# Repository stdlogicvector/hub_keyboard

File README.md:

# HUB Keyboard

A custom built 80% keyboard with an OLED and an integrated USB hub.

(The  can be found here.)

## Circuit Board

The circuit board is designed in Eagle.
For easy manufacturing, the gerber-files and SMT production files are included.

The BOM and SMT placement file (CPL) are formatted for use with JLCPCB.

Apart from the keys, display, and the USB-connector all parts can be populated by JLCPCB.
The schematic contains the LCSC partnumbers in the attributes of each part.

### JLCPCB Configuration

If you want to order PCBs from JLC-PCB with the provided gerber-files,
use the following settings after uploading the zipped gerber folder:

* Layers: 2
* Dimension: 362mm x 128.5mm
* PCB Color: Choose what you want
* PCB Thickness: 1.6
* Impedance: no
* Surface Finish: HASL(with lead) (ENIG is also OK)
* Copper Weight: 1
* Gold Fingers: No
* Material Details: FR4-Standard Tg 130-140C
* Panel By JLCPCB: No
* Flying Probe Test: Fully Test
* Castellated Holes: no
* Different Design: 1
* Remove Order Number: Choose what you want

5 PCBs without assembly cost about 17.35€ or $19.60.

If you want to have the SMT parts populated, choose "SMT Assembly" and select "Bottom Layer".

When asked for the BOM and CPL file, upload the provided files.

Assembly and parts for 5 PCBs costs about 45.50€ or $55.90.

### Keys

All keys compatible with Cherry MX 2 or 3 pin should fit the board.
There a mounting holes for the US-layout (with 2.25U Left Shift) and the EU-layout (with <> next to 1.25U Left Shift).
The Spacebar can also be replaced by up 5 individual keys.

### Display

The display is an 0.91" 128x32 SPI OLED module like [this](https://www.ebay.com/itm/312892164528). They are all over ebay and aliexpress.

### Misc Parts

The USB Connectors can be found on Digikey, but you can substitute others with the same pad layout.#

* USB-C : [Digikey](https://www.digikey.com/short/zm17vb)
* USB-A : [Digikey](https://www.digikey.com/short/zm1tcc)

## QMK Configuration

The folder qmk_config contains the configuration and code to build QMK for the HUB-Keyboard.
Just put this folder in qmk/keyboards and run

```
make hub_keyboard/v1:default
```	
	
## Plate & Case

Plate and Case are available as DXF and STL files. The Case also comes in two halves for easier printing. The DXF contains lines for both layout options at the left shift key. Delete what you don't need before cutting.

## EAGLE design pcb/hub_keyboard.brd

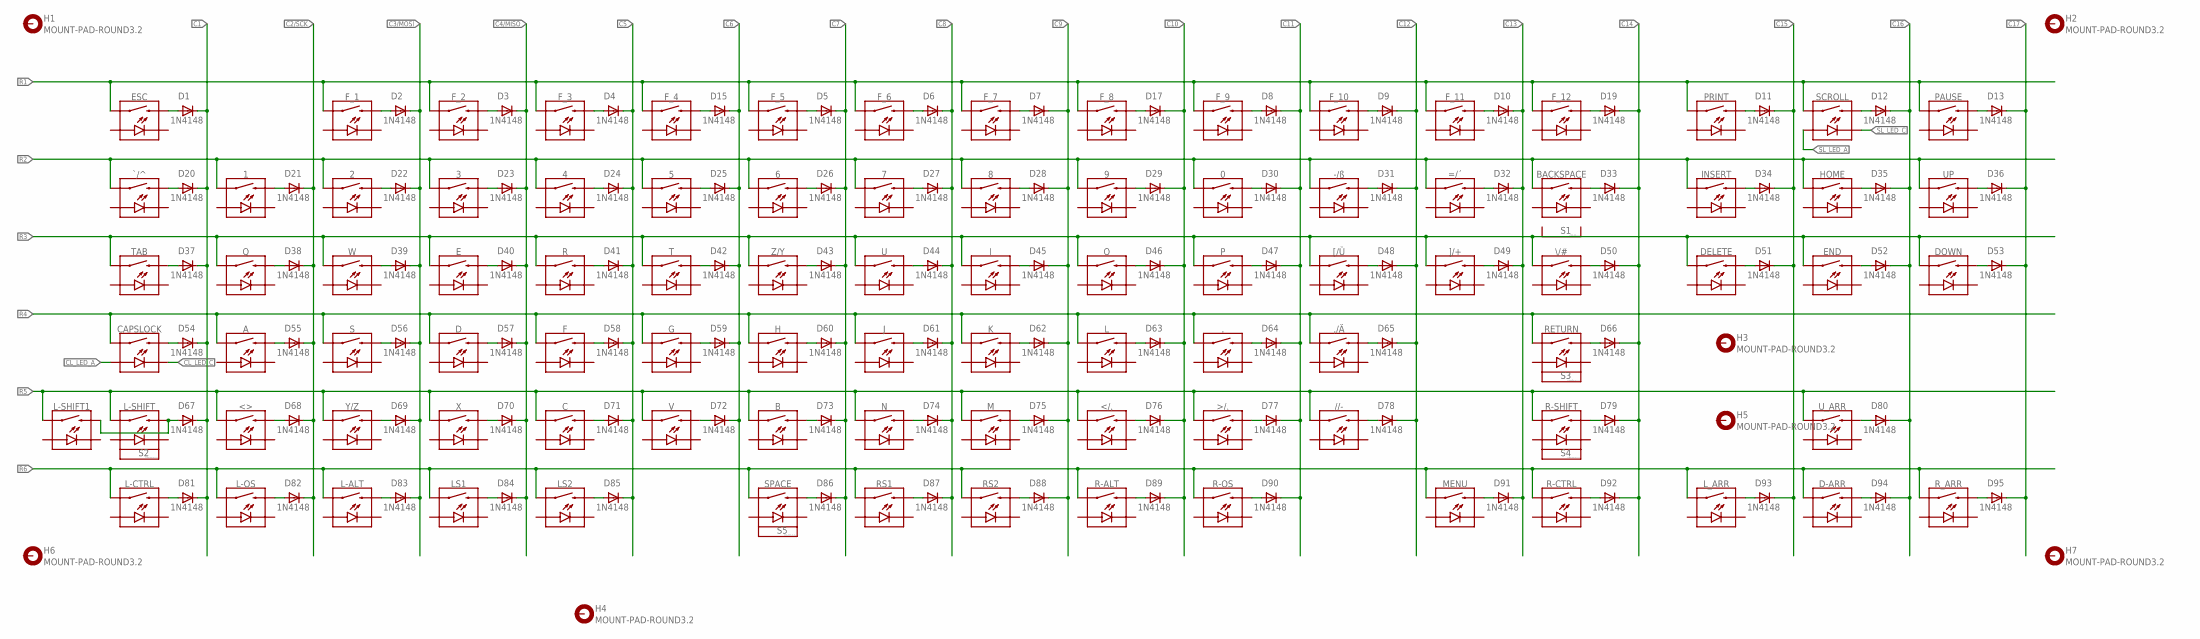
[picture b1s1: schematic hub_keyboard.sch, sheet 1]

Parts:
0, 1, 2, 3, 4, 5, 6, 7, 8, 9, .: MECHANICAL-KEYBOARD1U; CHERRY-MX-LED-1U
,/Ä: MECHANICAL-KEYBOARD1U; CHERRY-MX-LED-1U
-/ß: MECHANICAL-KEYBOARD1U; CHERRY-MX-LED-1U
//-: MECHANICAL-KEYBOARD1U; CHERRY-MX-LED-1U
</,: MECHANICAL-KEYBOARD1U; CHERRY-MX-LED-1U
<>: MECHANICAL-KEYBOARD1U; CHERRY-MX-LED-1U
=/´: MECHANICAL-KEYBOARD1U; CHERRY-MX-LED-1U
>/.: MECHANICAL-KEYBOARD1U; CHERRY-MX-LED-1U
A: MECHANICAL-KEYBOARD1U; CHERRY-MX-LED-1U
B: MECHANICAL-KEYBOARD1U; CHERRY-MX-LED-1U
BACKSPACE: MECHANICAL-KEYBOARD2U; CHERRY-MX-LED-1X2U
C: MECHANICAL-KEYBOARD1U; CHERRY-MX-LED-1U
CAPSLOCK: MECHANICAL-KEYBOARD1.75U; CHERRY-MX-LED-1.75U
D: MECHANICAL-KEYBOARD1U; CHERRY-MX-LED-1U
D1, D2, D3, D4, D5, D6, D7, D8, D9, D10, D11, D12, D13, D15, D17, D19, D20, D21, D22, D23, D24, D25, D26, D27, D28, D29, D30, D31, D32, D33, D34, D35, D36, D37, D38, D39, D40, D41, D42, D43, D44, D45, D46, D47, D48, D49, D50, D51, D52, D53, D54, D55, D56, D57, D58, D59, D60, D61, D62, D63, D64, D65, D66, D67, D68, D69, D70, D71, D72, D73, D74, D75, D76, D77, D78, D79, D80, D81, D82, D83, D84, D85, D86, D87, D88, D89, D90, D91, D92, D93, D94, D95: 1N4148; SOD123; LCSC C81598
D-ARR: MECHANICAL-KEYBOARD1U; CHERRY-MX-LED-1U
DELETE: MECHANICAL-KEYBOARD1U; CHERRY-MX-LED-1U
DOWN: MECHANICAL-KEYBOARD1U; CHERRY-MX-LED-1U
E: MECHANICAL-KEYBOARD1U; CHERRY-MX-LED-1U
END: MECHANICAL-KEYBOARD1U; CHERRY-MX-LED-1U
ESC: MECHANICAL-KEYBOARD1U; CHERRY-MX-LED-1U
F: MECHANICAL-KEYBOARD1U; CHERRY-MX-LED-1U
F_1, F_2, F_3, F_4, F_5, F_6, F_7, F_8, F_9, F_10, F_11, F_12: MECHANICAL-KEYBOARD1U; CHERRY-MX-LED-1U
G: MECHANICAL-KEYBOARD1U; CHERRY-MX-LED-1U
H: MECHANICAL-KEYBOARD1U; CHERRY-MX-LED-1U
H1, H2, H3, H4, H5, H6, H7: MOUNT-PAD-ROUND3.2; 3,2-PAD
HOME: MECHANICAL-KEYBOARD1U; CHERRY-MX-LED-1U
I: MECHANICAL-KEYBOARD1U; CHERRY-MX-LED-1U
INSERT: MECHANICAL-KEYBOARD1U; CHERRY-MX-LED-1U
J: MECHANICAL-KEYBOARD1U; CHERRY-MX-LED-1U
K: MECHANICAL-KEYBOARD1U; CHERRY-MX-LED-1U
L: MECHANICAL-KEYBOARD1U; CHERRY-MX-LED-1U
L-ALT: MECHANICAL-KEYBOARD1.25U; CHERRY-MX-LED-1.25U
L-CTRL: MECHANICAL-KEYBOARD1.25U; CHERRY-MX-LED-1.25U
L-OS: MECHANICAL-KEYBOARD1.25U; CHERRY-MX-LED-1.25U
L-SHIFT: MECHANICAL-KEYBOARD2.25U; CHERRY-MX-LED-1X2.25
L-SHIFT1: MECHANICAL-KEYBOARD1.25U; CHERRY-MX-LED-1.25U
LS1, LS2: MECHANICAL-KEYBOARD1.25U; CHERRY-MX-LED-1.25U
L_ARR: MECHANICAL-KEYBOARD1U; CHERRY-MX-LED-1U
M: MECHANICAL-KEYBOARD1U; CHERRY-MX-LED-1U
MENU: MECHANICAL-KEYBOARD1.25U; CHERRY-MX-LED-1.25U
N: MECHANICAL-KEYBOARD1U; CHERRY-MX-LED-1U
O: MECHANICAL-KEYBOARD1U; CHERRY-MX-LED-1U
P: MECHANICAL-KEYBOARD1U; CHERRY-MX-LED-1U
PAUSE: MECHANICAL-KEYBOARD1U; CHERRY-MX-LED-1U
PRINT: MECHANICAL-KEYBOARD1U; CHERRY-MX-LED-1U
Q: MECHANICAL-KEYBOARD1U; CHERRY-MX-LED-1U
R: MECHANICAL-KEYBOARD1U; CHERRY-MX-LED-1U
R-ALT: MECHANICAL-KEYBOARD1.25U; CHERRY-MX-LED-1.25U
R-CTRL: MECHANICAL-KEYBOARD1.25U; CHERRY-MX-LED-1.25U
R-OS: MECHANICAL-KEYBOARD1.25U; CHERRY-MX-LED-1.25U
R-SHIFT: MECHANICAL-KEYBOARD2.75U; CHERRY-MX-LED-1X2.75
RETURN: MECHANICAL-KEYBOARD2.25U; CHERRY-MX-LED-1X2.25
RS1, RS2: MECHANICAL-KEYBOARD1.25U; CHERRY-MX-LED-1.25U
R_ARR: MECHANICAL-KEYBOARD1U; CHERRY-MX-LED-1U
S: MECHANICAL-KEYBOARD1U; CHERRY-MX-LED-1U
S1: STABILIZER-1X2U; STABILIZER_1X2U
S2, S3: STABILIZER-1X2.25U; STABILIZER_1X2.25U
S4: STABILIZER-1X2.75U; STABILIZER_1X2.75U
S5: STABILIZER-1X6.25U; STABILIZER_1X6.25U
SCROLL: MECHANICAL-KEYBOARD1U; CHERRY-MX-LED-1U
SPACE: MECHANICAL-KEYBOARD6.25U; CHERRY-MX-LED-1X6.25
T: MECHANICAL-KEYBOARD1U; CHERRY-MX-LED-1U
TAB: MECHANICAL-KEYBOARD1.5U; CHERRY-MX-LED-1.5U
U: MECHANICAL-KEYBOARD1U; CHERRY-MX-LED-1U
UP: MECHANICAL-KEYBOARD1U; CHERRY-MX-LED-1U
U_ARR: MECHANICAL-KEYBOARD1U; CHERRY-MX-LED-1U
V: MECHANICAL-KEYBOARD1U; CHERRY-MX-LED-1U
W: MECHANICAL-KEYBOARD1U; CHERRY-MX-LED-1U
X: MECHANICAL-KEYBOARD1U; CHERRY-MX-LED-1U
Y/Z: MECHANICAL-KEYBOARD1U; CHERRY-MX-LED-1U
Z/Y: MECHANICAL-KEYBOARD1U; CHERRY-MX-LED-1U
[/Ü: MECHANICAL-KEYBOARD1U; CHERRY-MX-LED-1U
\\/#: MECHANICAL-KEYBOARD1.5U; CHERRY-MX-LED-1.5U
]/+: MECHANICAL-KEYBOARD1U; CHERRY-MX-LED-1U
`/^: MECHANICAL-KEYBOARD1U; CHERRY-MX-LED-1U

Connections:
C1: D1.C, D20.C, D37.C, D54.C, D67.C, D81.C; also elsewhere on the board
C2/SCK: D21.C, D38.C, D55.C, D68.C, D82.C; also elsewhere on the board
C3/MOSI: D2.C, D22.C, D39.C, D56.C, D69.C, D83.C; also elsewhere on the board
C4/MISO: D3.C, D23.C, D40.C, D57.C, D70.C, D84.C; also elsewhere on the board
C5: D4.C, D24.C, D41.C, D58.C, D71.C, D85.C; also elsewhere on the board
C6: D15.C, D25.C, D42.C, D59.C, D72.C; also elsewhere on the board
C7: D5.C, D26.C, D43.C, D60.C, D73.C, D86.C; also elsewhere on the board
C8: D6.C, D27.C, D44.C, D61.C, D74.C, D87.C; also elsewhere on the board
C9: D7.C, D28.C, D45.C, D62.C, D75.C, D88.C; also elsewhere on the board
C10: D17.C, D29.C, D46.C, D63.C, D76.C, D89.C; also elsewhere on the board
C11: D8.C, D30.C, D47.C, D64.C, D77.C, D90.C; also elsewhere on the board
C12: D9.C, D31.C, D48.C, D65.C, D78.C; also elsewhere on the board
C13: D10.C, D32.C, D49.C, D91.C; also elsewhere on the board
C14: D19.C, D33.C, D50.C, D66.C, D79.C, D92.C; also elsewhere on the board
C15: D11.C, D34.C, D51.C, D93.C; also elsewhere on the board
C16: D12.C, D35.C, D52.C, D80.C, D94.C; also elsewhere on the board
C17: D13.C, D36.C, D53.C, D95.C; also elsewhere on the board
CL_LED_A: CAPSLOCK.A; also elsewhere on the board
CL_LED_C: CAPSLOCK.K (C); also elsewhere on the board
unnamed: D11.A, PRINT.S2 (2)
unnamed: D34.A, INSERT.S2 (2)
unnamed: D51.A, DELETE.S2 (2)
unnamed: D12.A, SCROLL.S2 (2)
unnamed: D35.A, HOME.S2 (2)
unnamed: D93.A, L_ARR.S2 (2)
unnamed: D52.A, END.S2 (2)
unnamed: D80.A, U_ARR.S2 (2)
unnamed: D94.A, D-ARR.S2 (2)
unnamed: D13.A, PAUSE.S2 (2)
unnamed: D36.A, UP.S2 (2)
unnamed: D53.A, DOWN.S2 (2)
unnamed: <>.S2 (2), D68.A
unnamed: D95.A, R_ARR.S2 (2)
unnamed: D1.A, ESC.S2 (2)
unnamed: D20.A, `/^.S2 (2)
unnamed: D37.A, TAB.S2 (2)
unnamed: CAPSLOCK.S2 (2), D54.A
unnamed: D67.A, L-SHIFT.S2 (2), L-SHIFT1.S2 (2)
unnamed: D81.A, L-CTRL.S2 (2)
unnamed: 1.S2 (2), D21.A
unnamed: D38.A, Q.S2 (2)
unnamed: A.S2 (2), D55.A
unnamed: D69.A, Y/Z.S2 (2)
unnamed: D82.A, L-OS.S2 (2)
unnamed: D2.A, F_1.S2 (2)
unnamed: 2.S2 (2), D22.A
unnamed: D39.A, W.S2 (2)
unnamed: D56.A, S.S2 (2)
unnamed: D70.A, X.S2 (2)
unnamed: D83.A, L-ALT.S2 (2)
unnamed: D3.A, F_2.S2 (2)
unnamed: 3.S2 (2), D23.A
unnamed: D40.A, E.S2 (2)
unnamed: D.S2 (2), D57.A
unnamed: C.S2 (2), D71.A
unnamed: D4.A, F_3.S2 (2)
unnamed: 4.S2 (2), D24.A
unnamed: D41.A, R.S2 (2)
unnamed: D58.A, F.S2 (2)
unnamed: D72.A, V.S2 (2)
unnamed: D15.A, F_4.S2 (2)
unnamed: 5.S2 (2), D25.A
unnamed: D42.A, T.S2 (2)
unnamed: D59.A, G.S2 (2)
unnamed: B.S2 (2), D73.A
unnamed: D86.A, SPACE.S2 (2)
unnamed: D5.A, F_5.S2 (2)
unnamed: 6.S2 (2), D26.A
unnamed: D43.A, Z/Y.S2 (2)
unnamed: D60.A, H.S2 (2)
unnamed: D74.A, N.S2 (2)
unnamed: D6.A, F_6.S2 (2)
unnamed: 7.S2 (2), D27.A
unnamed: D44.A, U.S2 (2)
unnamed: D61.A, J.S2 (2)
unnamed: D75.A, M.S2 (2)
unnamed: D7.A, F_7.S2 (2)
unnamed: 8.S2 (2), D28.A
unnamed: D45.A, I.S2 (2)
unnamed: D62.A, K.S2 (2)
unnamed: </,.S2 (2), D76.A
unnamed: D17.A, F_8.S2 (2)
unnamed: 9.S2 (2), D29.A
unnamed: D46.A, O.S2 (2)
unnamed: D63.A, L.S2 (2)
unnamed: >/..S2 (2), D77.A
unnamed: D89.A, R-ALT.S2 (2)
unnamed: D8.A, F_9.S2 (2)
unnamed: 0.S2 (2), D30.A
unnamed: D47.A, P.S2 (2)
unnamed: ..S2 (2), D64.A
unnamed: //-.S2 (2), D78.A
unnamed: D90.A, R-OS.S2 (2)
unnamed: D9.A, F_10.S2 (2)
unnamed: -/ß.S2 (2), D31.A
unnamed: D48.A, [/Ü.S2 (2)
unnamed: ,/Ä.S2 (2), D65.A
unnamed: D10.A, F_11.S2 (2)
unnamed: =/´.S2 (2), D32.A
unnamed: D49.A, ]/+.S2 (2)
unnamed: D91.A, MENU.S2 (2)
unnamed: D19.A, F_12.S2 (2)
unnamed: BACKSPACE.S2 (2), D33.A
unnamed: D50.A, \\/#.S2 (2)
unnamed: D66.A, RETURN.S2 (2)
unnamed: D79.A, R-SHIFT.S2 (2)
unnamed: D92.A, R-CTRL.S2 (2)
unnamed: D85.A, LS2.S2 (2)
unnamed: D84.A, LS1.S2 (2)
unnamed: D88.A, RS2.S2 (2)
unnamed: D87.A, RS1.S2 (2)
R1: ESC.S1 (1), F_1.S1 (1), F_2.S1 (1), F_3.S1 (1), F_4.S1 (1), F_5.S1 (1), F_6.S1 (1), F_7.S1 (1), F_8.S1 (1), F_9.S1 (1), F_10.S1 (1), F_11.S1 (1), F_12.S1 (1), PAUSE.S1 (1), PRINT.S1 (1), SCROLL.S1 (1); also elsewhere on the board
R2: 0.S1 (1), 1.S1 (1), 2.S1 (1), 3.S1 (1), 4.S1 (1), 5.S1 (1), 6.S1 (1), 7.S1 (1), 8.S1 (1), 9.S1 (1), -/ß.S1 (1), =/´.S1 (1), BACKSPACE.S1 (1), HOME.S1 (1), INSERT.S1 (1), UP.S1 (1), `/^.S1 (1); also elsewhere on the board
R3: DELETE.S1 (1), DOWN.S1 (1), E.S1 (1), END.S1 (1), I.S1 (1), O.S1 (1), P.S1 (1), Q.S1 (1), R.S1 (1), T.S1 (1), TAB.S1 (1), U.S1 (1), W.S1 (1), Z/Y.S1 (1), [/Ü.S1 (1), \\/#.S1 (1), ]/+.S1 (1); also elsewhere on the board
R4: ,/Ä.S1 (1), ..S1 (1), A.S1 (1), CAPSLOCK.S1 (1), D.S1 (1), F.S1 (1), G.S1 (1), H.S1 (1), J.S1 (1), K.S1 (1), L.S1 (1), RETURN.S1 (1), S.S1 (1); also elsewhere on the board
R5: //-.S1 (1), </,.S1 (1), <>.S1 (1), >/..S1 (1), B.S1 (1), C.S1 (1), L-SHIFT.S1 (1), L-SHIFT1.S1 (1), M.S1 (1), N.S1 (1), R-SHIFT.S1 (1), U_ARR.S1 (1), V.S1 (1), X.S1 (1), Y/Z.S1 (1); also elsewhere on the board
R6: D-ARR.S1 (1), L-ALT.S1 (1), L-CTRL.S1 (1), L-OS.S1 (1), LS1.S1 (1), LS2.S1 (1), L_ARR.S1 (1), MENU.S1 (1), R-ALT.S1 (1), R-CTRL.S1 (1), R-OS.S1 (1), RS1.S1 (1), RS2.S1 (1), R_ARR.S1 (1), SPACE.S1 (1); also elsewhere on the board
SL_LED_A: SCROLL.A; also elsewhere on the board
SL_LED_C: SCROLL.K (C); also elsewhere on the board

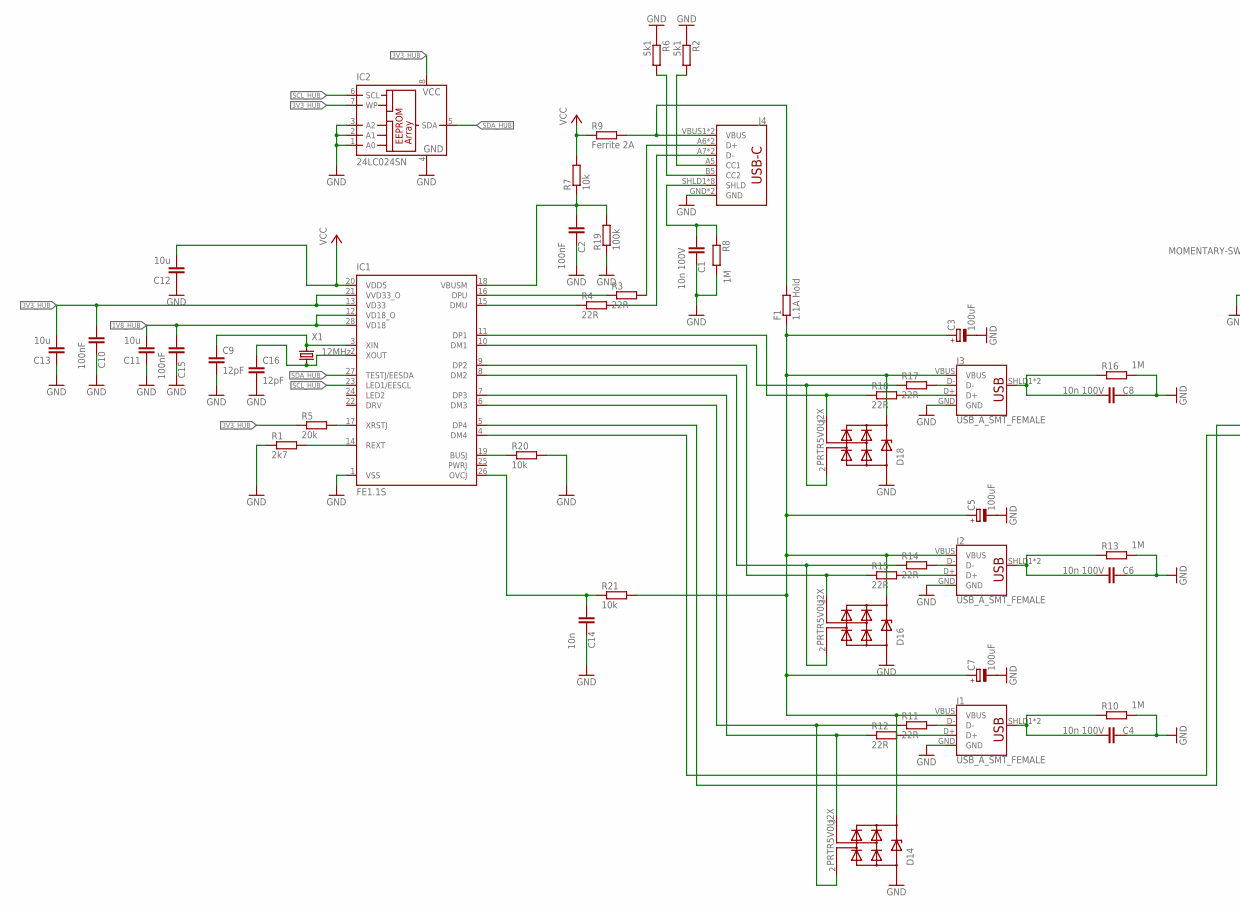
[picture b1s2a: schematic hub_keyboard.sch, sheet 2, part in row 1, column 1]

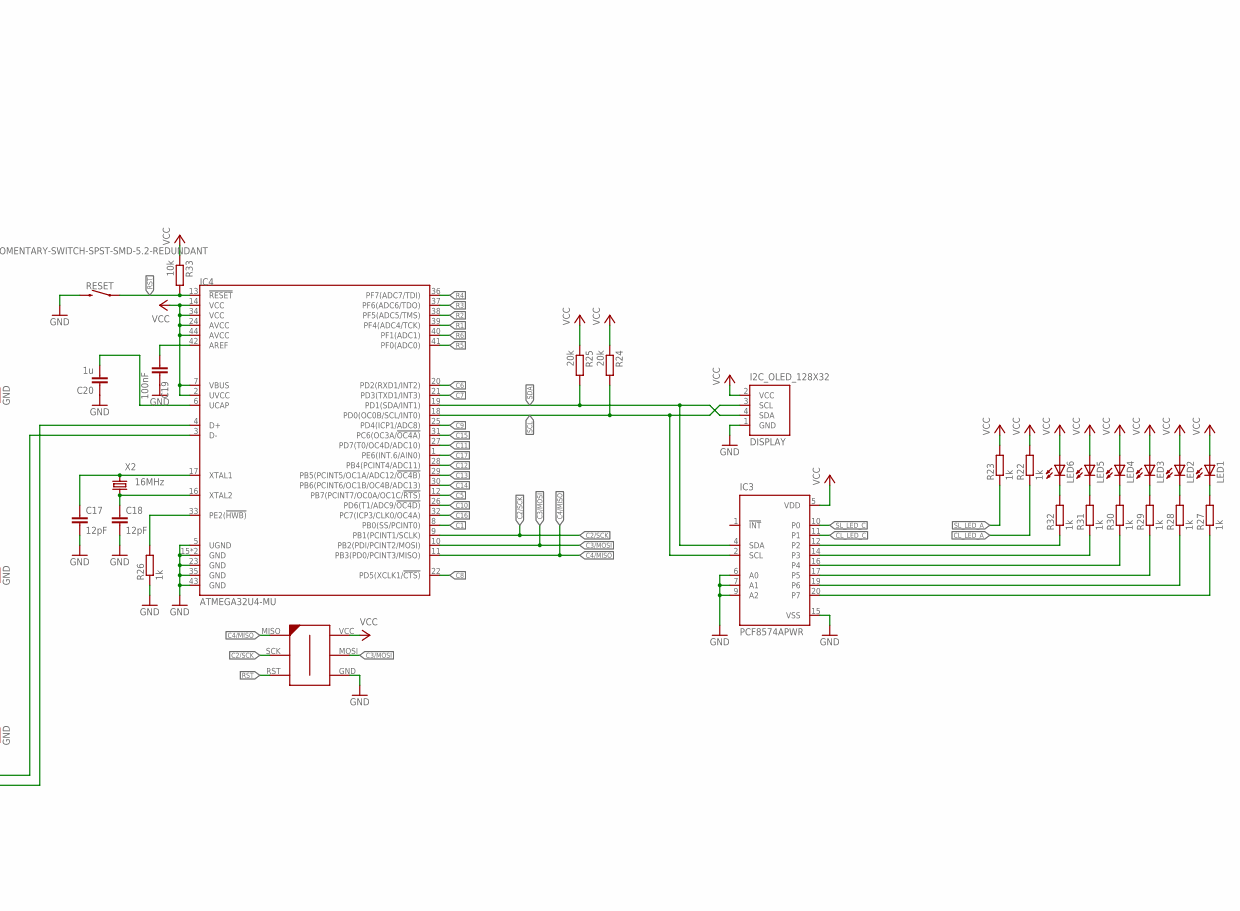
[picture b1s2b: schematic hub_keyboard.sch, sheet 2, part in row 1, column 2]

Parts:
C1, C4, C6, C8: 10n 100V; C0603; LCSC C84709
C2, C10, C15, C19: 100nF; C0603; LCSC C14663
C3, C5, C7: 100uF; CT3528; LCSC C16133
C9, C16, C17, C18: 12pF; C0603; LCSC C38523
C11, C12, C13: 10u; C0603; LCSC C19702
C14: 10n; C0603; LCSC C57112
C20: 1u; C0603; LCSC C15849
D14, D16, D18: PRTR5V0U2X; SOT143; DIGIKEY 1727-3884-1-ND
DISPLAY: I2C_OLED_128X32; 128X32_I2C_OLED
F1: 1.1A Hold; R1210; LCSC C70100
IC1: FE1.1S; SSOP28; LCSC C9359
IC2: 24LC024SN; SO-08; LCSC C184083
IC3: PCF8574APWR; SSOP20; LCSC C94361
IC4: ATMEGA32U4-MU; QFN44G-0.5-7X7MM; LCSC C112161
ISP: AVR-ISP-6-EDGE; 6PAD_ISP
J1, J2, J3: USB_A_SMT_FEMALE; USB-A-S-SILK-FEMALE; DIGIKEY 609-4946-1-ND
J4: USB_C2-LAYER; USB-C-16P; DIGIKEY 2073-USB4105-GF-ACT-ND
LED1, LED2, LED3, LED4, LED5, LED6: LED3MM
R1: 2k7; R0603; LCSC C13167
R2, R6: 5k1; R0603; LCSC C23186
R3, R4, R11, R12, R14, R15, R17, R18: 22R; R0603; LCSC C23345
R5, R24, R25: 20k; R0603; LCSC C4184
R7, R20, R21, R33: 10k; R0603; LCSC C25804
R8, R10, R13, R16: 1M; R0603; LCSC C22935
R9: Ferrite 2A; R0805; LCSC C44361
R19: 100k; R0603; LCSC C25803
R22, R23, R26, R27, R28, R29, R30, R31, R32: 1k; R0603; LCSC C21190
RESET: MOMENTARY-SWITCH-SPST-SMD-5.2-REDUNDANT; TACTILE_SWITCH_SMD_5.2MM; LCSC C318884
X1: 12MHz; 3.2X2.5_KX-7; LCSC C9002
X2: 16MHz; 3.2X2.5_KX-7; LCSC C13738

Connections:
1V8_HUB: C11.2, C15.2, IC1.12 (VD18_O), IC1.28 (VD18)
3V3_HUB: C10.2, C13.2, IC1.13 (VD33), IC1.21 (VVD33_O), IC2.7 (WP), IC2.8 (VCC), R5.1
C1: IC4.8 (PB0(SS/PCINT0)); also elsewhere on the board
C2/SCK: IC4.9 (PB1(PCINT1/SCLK)), ISP.SCK; also elsewhere on the board
C3/MOSI: IC4.10 (PB2(PDI/PCINT2/MOSI)), ISP.MOSI; also elsewhere on the board
C4/MISO: IC4.11 (PB3(PD0/PCINT3/MISO)), ISP.MISO; also elsewhere on the board
C5: IC4.12 (PB7(PCINT7/OC0A/OC1C/!RTS)); also elsewhere on the board
C6: IC4.20 (PD2(RXD1/INT2)); also elsewhere on the board
C7: IC4.21 (PD3(TXD1/INT3)); also elsewhere on the board
C8: IC4.22 (PD5(XCLK1/!CTS)); also elsewhere on the board
C9: IC4.25 (PD4(ICP1/ADC8)); also elsewhere on the board
C10: IC4.26 (PD6(T1/ADC9/!OC4D)); also elsewhere on the board
C11: IC4.27 (PD7(T0/OC4D/ADC10)); also elsewhere on the board
C12: IC4.28 (PB4(PCINT4/ADC11)); also elsewhere on the board
C13: IC4.29 (PB5(PCINT5/OC1A/ADC12/!OC4B)); also elsewhere on the board
C14: IC4.30 (PB6(PCINT6/OC1B/OC4B/ADC13)); also elsewhere on the board
C15: IC4.31 (PC6(OC3A/!OC4A)); also elsewhere on the board
C16: IC4.32 (PC7(ICP3/CLK0/OC4A)); also elsewhere on the board
C17: IC4.1 (PE6(INT.6/AIN0)); also elsewhere on the board
CL_LED_A: R22.1; also elsewhere on the board
CL_LED_C: IC3.11 (P1); also elsewhere on the board
GND: C1.1, C2.1, C3.-, C4.1, C5.-, C6.1, C7.-, C8.1, C9.2, C10.1, C11.1, C12.1, C13.1, C14.1, C15.1, C16.2, C17.2, C18.2, C19.1, C20.1, D14.1 (GND), D16.1 (GND), D18.1 (GND), DISPLAY.1 (GND), IC1.1 (VSS), IC2.1 (A0), IC2.2 (A1), IC2.3 (A2), IC2.4 (GND), IC3.6 (A0), IC3.7 (A1), IC3.9 (A2), IC3.15 (VSS), IC4.5 (UGND), IC4.15 (GND), IC4.23 (GND), IC4.35 (GND), IC4.43 (GND), IC4.TAB (GND), ISP.GND, J1.GND, J2.GND, J3.GND, J4.GND, J4.GND2 (GND), R1.1, R2.1, R6.1, R8.2, R10.2, R13.2, R16.2, R19.1, R20.2, R26.1, RESET.3 (2), RESET.4 (2)
unnamed: IC4.33 (PE2(!HWB)), R26.2
unnamed: IC1.17 (XRSTJ), R5.2
unnamed: IC1.14 (REXT), R1.2
unnamed: IC1.19 (BUSJ), R20.1
unnamed: J4.A5 (CC1), R2.2
unnamed: C3.+, C5.+, C7.+, D14.4 (VCC), D16.4 (VCC), D18.4 (VCC), F1.1, J1.VBUS, J2.VBUS, J3.VBUS, R21.2
unnamed: C14.2, IC1.26 (OVCJ), R21.1
unnamed: F1.2, J4.VBUS1 (VBUS), J4.VBUS2 (VBUS), R9.2
unnamed: D16.2 (IO1), IC1.8 (DM2), R14.1
unnamed: D16.3 (IO2), IC1.9 (DP2), R15.1
unnamed: D14.3 (IO2), IC1.7 (DP3), R12.1
unnamed: D14.2 (IO1), IC1.6 (DM3), R11.1
unnamed: J4.A7 (D-), J4.B7 (D-), R4.2
unnamed: J4.A6 (D+), J4.B6 (D+), R3.2
unnamed: C9.1, IC1.3 (XIN), X1.3 (2)
unnamed: IC1.15 (DMU), R4.1
unnamed: IC1.16 (DPU), R3.1
unnamed: IC1.4 (DM4), IC4.3 (D-)
unnamed: IC1.5 (DP4), IC4.4 (D+)
unnamed: C2.2, IC1.18 (VBUSM), R7.1, R19.2
unnamed: C17.1, IC4.17 (XTAL1), X2.3 (2)
unnamed: C18.1, IC4.16 (XTAL2), X2.1
unnamed: C20.2, IC4.6 (UCAP)
unnamed: C8.2, J3.SHLD1 (SHIELD), J3.SHLD2 (SHIELD), R16.1
unnamed: C6.2, J2.SHLD1 (SHIELD), J2.SHLD2 (SHIELD), R13.1
unnamed: C4.2, J1.SHLD1 (SHIELD), J1.SHLD2 (SHIELD), R10.1
unnamed: C1.2, J4.SHLD1 (SHLD), J4.SHLD2 (SHLD), J4.SHLD3 (SHLD), J4.SHLD4 (SHLD), J4.SHLD5 (SHLD), J4.SHLD6 (SHLD), J4.SHLD7 (SHLD), J4.SHLD8 (SHLD), R8.1
unnamed: J4.B5 (CC2), R6.2
unnamed: C19.2, IC4.42 (AREF)
unnamed: C16.1, IC1.2 (XOUT), X1.1
unnamed: LED6.K (C), R32.2
unnamed: LED5.K (C), R31.2
unnamed: LED4.K (C), R30.2
unnamed: LED3.K (C), R29.2
unnamed: LED2.K (C), R28.2
unnamed: LED1.K (C), R27.2
unnamed: IC3.12 (P2), R32.1
unnamed: IC3.14 (P3), R31.1
unnamed: IC3.16 (P4), R30.1
unnamed: IC3.17 (P5), R29.1
unnamed: IC3.19 (P6), R28.1
unnamed: IC3.20 (P7), R27.1
unnamed: J3.D-, R17.2
unnamed: J3.D+, R18.2
unnamed: J2.D-, R14.2
unnamed: J2.D+, R15.2
unnamed: J1.D-, R11.2
unnamed: J1.D+, R12.2
R1: IC4.39 (PF4(ADC4/TCK)); also elsewhere on the board
R2: IC4.38 (PF5(ADC5/TMS)); also elsewhere on the board
R3: IC4.37 (PF6(ADC6/TDO)); also elsewhere on the board
R4: IC4.36 (PF7(ADC7/TDI)); also elsewhere on the board
R5: IC4.41 (PF0(ADC0)); also elsewhere on the board
R6: IC4.40 (PF1(ADC1)); also elsewhere on the board
RST: IC4.13 (!RESET), ISP.RST, R33.2, RESET.1, RESET.2 (1)
SCL: DISPLAY.3 (SCL), IC3.2 (SCL), IC4.18 (PD0(OC0B/SCL/INT0)), R24.2
SCL_HUB: IC1.23 (LED1/EESCL), IC2.6 (SCL)
SDA: DISPLAY.4 (SDA), IC3.4 (SDA), IC4.19 (PD1(SDA/INT1)), R25.2
SDA_HUB: IC1.27 (TESTJ/EESDA), IC2.5 (SDA)
SL_LED_A: R23.1; also elsewhere on the board
SL_LED_C: IC3.10 (P0); also elsewhere on the board
USB1N: D18.2 (IO1), IC1.10 (DM1), R17.1
USB1P: D18.3 (IO2), IC1.11 (DP1), R18.1
VCC: C12.2, DISPLAY.2 (VCC), IC1.20 (VDD5), IC3.5 (VDD), IC4.2 (UVCC), IC4.7 (VBUS), IC4.14 (VCC), IC4.24 (AVCC), IC4.34 (VCC), IC4.44 (AVCC), ISP.VCC, LED1.A, LED2.A, LED3.A, LED4.A, LED5.A, LED6.A, R7.2, R9.1, R22.2, R23.2, R24.1, R25.1, R33.1

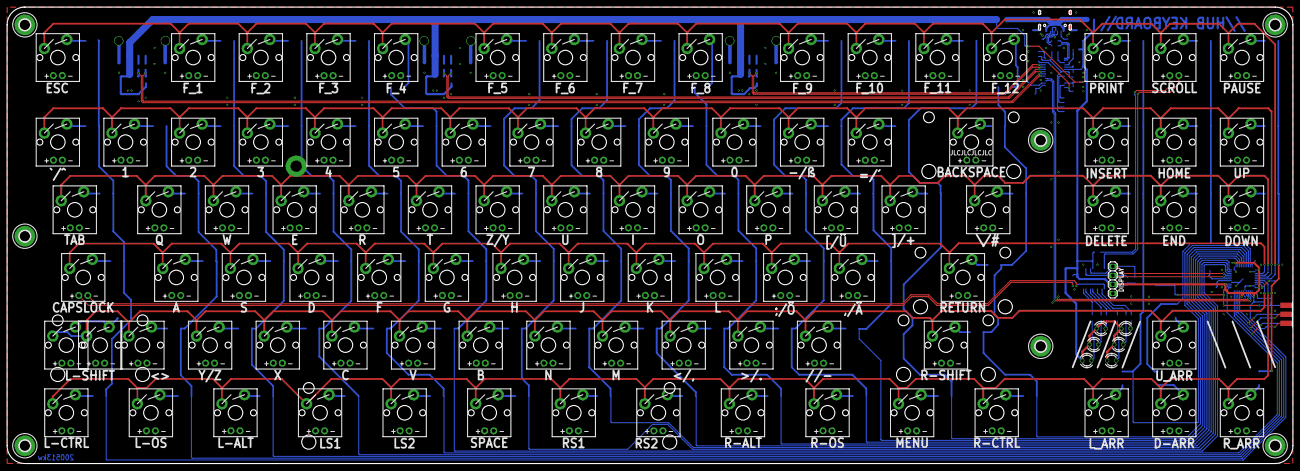
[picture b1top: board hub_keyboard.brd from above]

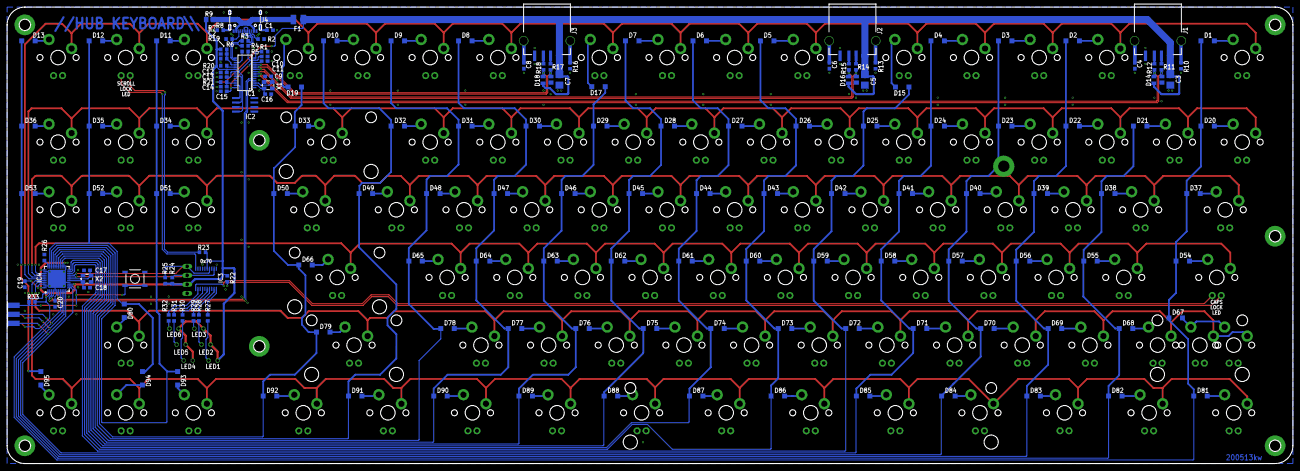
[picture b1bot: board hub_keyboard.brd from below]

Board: 2 copper layers, 362.0 x 128.5 mm, 273 parts (161 on the bottom side), 178 nets.

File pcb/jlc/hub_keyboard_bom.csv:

Comment,Designator,Footprint,LCSC
1.1A,F1,1210,C70100
1M,"R8, R10, R13, R16",0603,C22935
1N4148,"D1, D2, D3, D4, D5, D6, D7, D8, D9, D10, D11, D12, D13, D15, D17, D19, D20, D21, D22, D23, D24, D25, D26, D27, D28, D29, D30, D31, D32, D33, D34, D35, D36, D37, D38, D39, D40, D41, D42, D43, D44, D45, D46, D47, D48, D49, D50, D51, D52, D53, D54, D55, D56, D57, D58, D59, D60, D61, D62, D63, D64, D65, D66, D67, D68, D69, D70, D71, D72, D73, D74, D75, D76, D77, D78, D79, D80, D81, D82, D83, D84, D85, D86, D87, D88, D89, D90, D91, D92, D93, D94, D95",SOD123,C81598
1k,"R22, R23, R26, R27, R28, R29, R30, R31, R32",0603,C21190
1u,C20,0603,C15849
2k7,R1,0603,C13167
5k1,"R2, R6",0603,C23186
10k,"R7, R20, R21, R33",0603,C25804
10n,C14,0603,C57112
10n,"C1, C4, C6, C8",0603,C84709
10u,"C11, C12, C13",0603,C19702
12MHz,X1,SMD-3225_4P,C9002
12pF,"C9, C16, C17, C18",0603,C38523
16MHz,X2,SMD-3225_4P,C13738
20k,"R5, R24, R25",0603,C4184
22R,"R3, R4, R11, R12, R14, R15, R17, R18",0603,C23345
100k,R19,0603,C25803
100nF,"C2, C10, C15, C19",0603,C14663
100uF,"C3, C5, C7",3528,C16133
FE1.1S,IC1,SSOP-28,C9359
Ferrite,R9,0805,C44361
PCF8574APWR,IC3,TSSOP-20,C94361
PRTR5V0U2X,"D14, D16, D18",SOT-143,C384891
ATMEGA32U4-MU,IC4,QFN-44_EP_7x7x0.5P,C112161
SPST-SMD-5.2,RESET,SMD-5.2,C318884
24LC024SN,IC2,24LC024SN,C184083

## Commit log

2020-06-08 Added Gerbers
2020-12-13 Added Case & Plate files
    CAD files for a case and a plate. The case is also available as two halves for easier printing.
2021-06-17 Update README.md
    Fixed external links

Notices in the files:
parts and their libraries:
SparkFun-Switches: Licensing: Creative Commons ShareAlike 4.0 International - https://creativecommons.org/licenses/by-sa/4.0
crystal-geyer_V1_0: Copyright: Geyer-Electronic
